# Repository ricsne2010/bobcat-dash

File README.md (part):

# M.O.S.S.: Maintenance, Operations, and Service System

(The `bobcat-dash` project.) A full-screen gauge display for a 1978 Bobcat M700 skid steer (Wisconsin VH4D 4-cylinder gas engine,
PerTronix electronic ignition), running on a Raspberry Pi.

| Gauge / light | Sensor | Green | Amber | Red |
|---|---|---|---|---|
| Battery, engine off | ADS1115 ch 0 through a voltage divider | 12.2–14.8 V (`CHARGING` at 13.2 V and up, e.g. a battery charger) | 11.8–12.2 V (LOW), 14.8–15.5 V (HIGH) | < 11.8 V or > 15.5 V |
| Battery, engine running | same | 13.2–14.8 V (CHARGING) | 12.0–13.2 V (NOT CHARGING), 14.8–15.5 V (HIGH) | < 12.0 V or > 15.5 V |
| Fuel level | ADS1115 ch 1, fuel sender | > 25 % | ≤ 25 % | ≤ 12 % |
| Tachometer | GPIO 17, from the ignition coil's negative terminal (PerTronix) through the board's coil input | 800–3050 rpm (VH4D governed ≈2950 no-load) | LOW IDLE (600–800 rpm for 1 s while running), 3050–3200 rpm | ≥ 3200 rpm (overspeed) |
| Engine oil pressure | GPIO 22, original switch through an optocoupler | OK | | LOW (flashing) |
| Hydraulic filter bypass | ADS1115 A2, monitored (4.7 kΩ resistor at the switch) | OK | | BYPASS (flashing) |
| Hydraulic oil temp | ADS1115 A3, monitored (4.7 kΩ resistor at the switch) | OK | | HOT (flashing) |

The battery panel switches between its engine-off and engine-running limits automatically, and its
color bar redraws to match. A caption in the panel's corner shows which set is active.

Grey means **no signal**: a broken wire, an unplugged sender, or an ADC that isn't answering. The filter
and temp switches are **monitored**: a resistor at each switch lets the dash spot a broken or unplugged
wire, which otherwise would look like a healthy open switch (see [End-of-line resistors](#end-of-line-resistors-filter-and-temp-switches)). The
header shows a summary: `ALL OK`, `CHECK n`, or a flashing `n ALARMS`. Every threshold is
in `config.toml`.

On startup, all warning tiles flash red for 2 seconds as a **lamp test**, like an old bulb check.
With the engine stopped, the oil-pressure switch is always closed, so that tile shows grey
`ENGINE OFF` instead of red.

The **tach decides** whether the engine is running. If it reads 0 rpm but the battery is at charging
voltage (13.2 V or more), the **oil pressure switch** settles it:

| Tach | Battery | Oil pressure | Means | Dash shows |
|---|---|---|---|---|
| 0 rpm | 13.2 V+ | none | Parked with a **battery charger** connected | `ENGINE OFF`, green `CHARGING`, no warnings |
| 0 rpm | 13.2 V+ | present | Engine running, **tach sensor dead** | `ENGINE RUNNING`, amber `CHECK SENSOR` on the tach |

Once a dead tach has been seen on a running engine, the dash remembers it until the alternator voltage
drops (engine stopped) or the tach reads again. If oil pressure is lost in that time, it's still a red
alarm with the horn. A charger on a parked machine can't set off the horn, and a dead tach can't hide
low oil pressure.

---

## Parts list

The full list with part numbers and quantities is the spreadsheet [`docs/bobcat-dash-BOM.xlsx`](docs/bobcat-dash-BOM.xlsx) (made by `tools/diagrams/make_bom.py`). The main parts:

| Part | Notes |
|---|---|
| Raspberry Pi 4 (2 GB is plenty) or Pi 5 | |
| Weatherproof HDMI monitor with its own 12 V supply, 1024×768 or similar | Any resolution works because the layout scales. Sunlight-readable (≥ 800 nits) helps a lot outdoors. Wiring: see [Monitor and boot splash](#monitor-and-boot-splash). |
| 12 V automotive relay (30/40 A, with socket) + fuse holder | Feeds the LED lights through the key. See [Lights](#lights). |
| 3× inline fuse holder, 1 A | One on each light sense wire, where it taps into the light circuit |
| ADS1115 16-bit ADC breakout | I2C, 4 channels: battery, fuel, filter, temp |
| 2× PC817 optocoupler | Oil pressure and tach. Keeps 12 V off the Pi. |
| 12 V → 5 V automotive buck converter, **5 A** (8–36 V input) | Don't use a cigarette-lighter USB plug. Pi 5 needs 5 A. |
| Inline fuse holder, 3 A | On the 12 V feed from the ignition switch (hand-wired). With the breakout board rev 2.0: 7.5 A at the battery on the constant feed, plus 2 A on the IGN wire. |
| Resistors: 47 kΩ, 4× 10 kΩ, 220 Ω, 2× 2.2 kΩ, 3× 4.7 kΩ, 100 Ω | |
| 2× 4.7 kΩ ½ W metal film resistor | **End-of-line resistors**, fitted at the filter and temp switches |
| 8× BAT85 Schottky diode | Clamp the ADC inputs (one to 3.3 V, one to GND, per input A0–A3) |
| 2× 1N4148 diode, 4× 0.1 µF capacitor | |
| Tach signal: a wire from the ignition coil's **negative** terminal | This machine (PerTronix + Flame-Thrower 40611 coil) uses the breakout board's COIL input (its own `COIL` plug since rev 2.4). A NJK-5002C Hall sensor + magnet on the crank pulley is the alternative, and the only option when hand-wiring. |
| Weatherproof enclosure, Deutsch/Weatherpack connectors | Vibration kills loose Dupont jumpers |

## Wiring

All Pi-side grounds connect together: Pi GND, ADS1115 GND, and the optocoupler output side.
The 12 V side of the optocouplers stays separate from the Pi side.

```
POWER (hand-wired: the Pi loses power the moment the key is turned off)
  Ignition switch (+12V) ──[3A fuse]──> Buck converter IN+ ──> 5V OUT ──> Pi USB-C / 5V pins
  Chassis ground ──────────────────────> Buck converter IN- ──> GND

POWER (breakout board rev 2.0: clean shutdown at key-off, see "Key-off shutdown")
  Battery + ──[7.5A fuse, at the battery]──> board POWER IN "BAT+"   (constant, always live)
  Key switch IGN terminal ──[2A fuse]──────> board POWER IN "IGN"    (a few mA: sense only)
  Chassis ground ──────────────────────────> board POWER IN "GND"
  Board "TO BUCK" ──> Buck converter IN+ / IN-  (switched by the board)

ADS1115                     Pi
  VDD ───────────────────── 3.3V (pin 1)
  GND ───────────────────── GND  (pin 6)
  SDA ───────────────────── GPIO2 / SDA (pin 3)
  SCL ───────────────────── GPIO3 / SCL (pin 5)
  ADDR ──────────────────── GND  (address 0x48)

BATTERY VOLTAGE  -> ADS1115 A0
  +12V (ignition) ──[47k]──┬──────────> A0
                           ├──[10k]───> GND
                           ├──[BAT85, band toward 3.3V]──> 3.3V
                           ├──[BAT85, band toward A0]────> GND
                           └──[0.1µF]──> GND
  The BAT85s only conduct if A0 goes above 3.3 V or below 0 V. Don't use a 3.3 V zener here:
  low-voltage zeners leak tens of µA, which would pull the battery reading low.
  Ratio = (47+10)/10 = 5.7, so 15.5 V reads as 2.72 V on the ADC.

FUEL SENDER  -> ADS1115 A1
  Setup A, sender wired only to the dash:
      3.3V ──[220Ω]──┬──> A1           (+ two BAT85 clamps and 0.1µF, as for A0)
                     └──> sender terminal (the sender grounds through the tank)
  Setup B, an analog gauge as well (a backup if the Pi or monitor fails):
      12V (key) ──> gauge ──> sender terminal ──[47k]──┬──> A1   (no 220Ω pull-up)
                                                        └──[10k]──> GND
  The breakout board does either with jumpers JP1/JP2. Calibrate with --calibrate (below).

OIL PRESSURE SWITCH  -> GPIO 22, through an optocoupler
  The oil switch closes to ground when pressure is low.

  +12V (ignition) ──[2.2k]──> PC817 LED anode (+)
  PC817 LED cathode (-) ────> oil switch terminal
  1N4148 across the LED, reversed (protects it from voltage spikes)

  PC817 collector ──> GPIO 22      (Pi internal pull-up is enabled)
  PC817 emitter ────> Pi GND

  Switch closes -> LED lights -> GPIO pulled low -> alarm.

HYD FILTER BYPASS + HYD OIL TEMP SWITCHES  -> ADS1115 A2 / A3, monitored
  At each switch: a 4.7k "end-of-line" resistor from the switch terminal to ground
  (see "End-of-line resistors" below). At the Pi end, for each switch:

  3.3V ──[4.7k]──┬──[10k]──┬──> A2 (filter) / A3 (temp)
                 │         ├──[BAT85, band toward 3.3V]──> 3.3V
                 │         ├──[BAT85, band toward A2]────> GND
                 │         └──[0.1µF]──> GND
                 └──────────> switch wire (to the switch + its 4.7k resistor)

  Wire reads ~1.65 V = OK, ~0 V = switch closed (alarm), 3.3 V = wire broken (NO SIGNAL).
  Nothing else may connect to these two switches (no lamps): any 12 V on the wire reads as "broken".

  Optional status LEDs driven by the Pi: GPIO 23 (filter) / GPIO 24 (temp) ──[470Ω]──> LED ──> GND.
  On = switch closed, blinking = wire broken, off = OK.

TACH  -> GPIO 17   (hand-wired: Hall sensor only. For the ignition coil, use the breakout board's COIL input.)
  NJK-5002C Hall sensor: brown = +12V, blue = ground, black = signal (NPN, pulls low near a magnet)
  +12V ──[2.2k]──> PC817 LED anode;  LED cathode ──> sensor black wire
  PC817 collector ──> GPIO 17, plus a 4.7k pull-up to 3.3V (faster edges than the internal one)
  PC817 emitter ──> Pi GND
```

> **Tach from the ignition coil (this machine).** The Wisconsin VH4D has a PerTronix electronic
> distributor and a Flame-Thrower 40611 coil (3.0 Ω). The tach reads the coil's **negative (−)
> terminal**, the same place a normal aftermarket tach connects, on the breakout board's **COIL** plug (the
> 2-pin plug on the board's left edge, inside the boxed HIGH VOLTAGE corner; rev 2.4). Each spark is one pulse, and a 4-cylinder four-stroke fires twice per crank turn, so
> `pulses_per_rev = 2.0`.
>
> That terminal jumps to about 300–400 V every time the coil fires, so it must **only** go to the COIL
> plug, never to TACH SIG or any other input. The board's coil input is built for it: two ½ W resistors take the
> voltage, a 15 V zener clamps it, and a 1 µF capacitor smooths the coil's ringing so each spark gives one
> clean pulse into its own optocoupler. The software also ignores anything within 3 ms of a pulse
> (`min_pulse_gap_ms`), as a second line of defence. Run a 20 AWG wire from the coil − terminal to the
> board, away from the spark plug leads. Shielded wire is better still: connect the shield's drain to the
> COIL plug's GND pin and leave it unconnected at the coil end. Per PerTronix, this coil needs **no ballast resistor** or resistance
> wire in its + feed.
>
> No sensor, magnet or bracket is needed on the crank pulley. The trade-off: if the ignition stops, the tach
> reads 0. That's fine, because the engine has stopped too.

## Low idle and cool-down

**LOW IDLE** (amber, one soft beep). If the engine is running but sits below 800 rpm for more than
a second, the RPM pill turns amber and reads `LOW IDLE`. The dial shows the same band in amber, from
600 to 800 rpm. A sagging idle usually means a stall is coming: fuel starving, a plugged
fuel filter, the choke left on, or carb icing. It's ignored for the first 5 s after start-up.
Set `low_idle_below = 0` in `[tach]` to turn it off.

**Cool-down reminder** (information only: no sound, and not a warning). The VH4D is air-cooled, and the
repair manual says to idle it at 1000–1200 rpm for 3–5 minutes after hard running before shutting off.
The dash keeps track:

1. Time at or above 2000 rpm adds up as hard work. Short dips don't reset it.
2. Once there's 5 minutes of it, bring the hand throttle back to idle (1300 rpm or below). The RPM pill
   then counts down: `COOL DOWN 2:40`.
3. Rev above 1300 rpm and the countdown starts over. At part throttle (1300–2000 rpm) the pill says
   `IDLE TO COOL DOWN`.
4. When it's done: `OK TO SHUT DOWN` in green for a minute.

Stopping the engine clears it. The numbers are in `[cooldown]` in `config.toml`.

## Machine angle (roll and pitch)

The **MACHINE ANGLE** panel shows the machine from behind (roll, side to side) and from the side (pitch, nose
up or down). The outlines tilt with the machine, over a dashed level line, with the angle in degrees and which
way it's leaning. Battery and fuel share the panel above it, and the warning tiles are a little shorter to make
room.

| | Amber `STEEP` (one beep) | Red `TIP RISK` (alarm tone + horn) |
|---|---|---|
| Roll (either side) | 8° | 15° |
| Pitch, nose up | 15° | 20° |
| Pitch, nose down (backing up a steep incline) | 20° | 25° |

**These limits are not from Bobcat.** Bobcat's manuals give no angles: they say to keep the heavy end of the
loader uphill and to travel straight up and down slopes, never across. These defaults are chosen for this
machine: roll warns earliest because side slopes are where a skid steer is least stable, and nose down allows
the most because steep inclines are backed up, with the nose pointing downhill and the heavy end uphill. Change them in `[tilt]`, and use
lower limits if you often work with a loaded or raised bucket. An angle must last 0.5 s before it shows (a bump
isn't a slope), and clears 1° back inside the limit.

**Sensor:** an **LSM6DSOX** accelerometer + gyro board (Adafruit 4438, or the LSM6DS3TR-C, Adafruit 4503). It plugs
into the breakout board's latching **TILT** connector (Molex Micro-Fit 3.0, rev 2.6): pin 1 GND, 2 3V3, 3 SDA,
4 SCL. Make the cable from 22–24 AWG wire (4-core shielded is best): a Micro-Fit housing 43645-0400 with four
43030-0007 crimp pins at the board end, and the other end soldered straight into the sensor board's VIN, GND,
SDA and SCL holes (its small STEMMA QT socket is friction-only and would shake loose). It shares the Pi's I2C
bus with the ADS1115.

**Cable length:** I2C is meant for short runs, and a skid steer is electrically noisy. Under ~30 cm is ideal;
up to ~50 cm is fine routed away from the coil and plug leads (shielded 4-core is better, shield grounded at
the board end only). Up to ~1 m, also slow the bus with `dtparam=i2c_arm_baudrate=50000` in
`/boot/firmware/config.txt`. Further than that, use a differential I2C extender (e.g. SparkFun QwiicBus,
PCA9615). The dash blends the gyro and accelerometer, so
braking, bouncing and turning don't make the angle jump.

- **Mount it rigidly** to the frame, or inside a dash box that's bolted solidly to it (not on rubber
  isolators). Flat, with the board's **X arrow pointing forward**. Other orientations: `axes` and `upside_down`
  in `[tilt]`.
- **Zero it once**, parked on level, firm ground with the engine off: `python3 dash.py --zero-tilt`. It saves
  the level point (and the gyro's small offset) in the data folder, where it stays through every key-off. It
  refuses if the sensor reads more than 5° off level (parked on a slope, or the sensor mounted crooked) or if
  the readings move (engine running, someone climbing on). Add `--force` only if you're sure the machine is
  level.
- **Parking and restarting on a slope is fine.** Nothing needs remembering: gravity gives the true angle at
  every start-up. The first second is averaged (during the boot splash) so engine vibration doesn't skew
  it. If you're parked past a limit, the panel says so as soon as the dash is up.
- **If the sensor is missing or fails, the panel shows grey NO SIGNAL, never a guessed "level".** It counts
  as `CHECK` in the header and plays the connection-lost sound once; nothing else on the dash is affected.
  The dash keeps trying: a sensor plugged in later is picked up within about 2 s. A plug that works loose
  and back in, or a power blip, makes the chip restart powered down and read all zeros; that's caught
  (along with any reading where gravity isn't about 1 g, or the chip losing its settings), and the sensor is
  set up again and re-averaged for a second before an angle shows. A single glitchy read is ignored. Each
  problem is written once to the log (`journalctl -u bobcat-dash`).
- To leave tilt out entirely, set
  `enabled = false` in `[tilt]`: the screen goes back to the original layout (separate battery and fuel panels,
  taller warning tiles).

## Temperatures

The header shows temperatures next to **BOBCAT**: the electronics box (E-box) air, then your probes.

```
BOBCAT   E-BOX 100°F   CAB 92°F   OUT 104°F          ENGINE RUNNING              ALL OK
```

- **E-BOX** (electronics box) is the DS18B20 on the breakout board (rev 2.7): the air inside its enclosure. Above **50 °C
  (122 °F)** it turns into an amber **E-BOX HOT** pill (one beep, counts in `CHECK`); above **65 °C (149 °F)** red
  (alarm tone, no horn). The breakout board's own parts are rated well above that; the limits warn you that
  the box is cooking (no ventilation, direct sun) before anything else in it suffers. If the board sensor
  stops answering it shows grey `BOX --` (and the connection-lost sound).
- **Probes:** waterproof DS18B20 probes (stainless tip on a cable, 3-wire) plugged into the board's
  **TEMP PROBE** connector: red to 3V3, black to GND, yellow (or white) to DQ. Several can share the one
  connector (splice them together, or use a small junction). Each shows by the name you give it, e.g. `CAB`
  and `OUT`, or set `ambient = "average"` for a single `AMB` reading. A missing probe shows `--`.
- **Setup:** once, `dtoverlay=w1-gpio` in `/boot/firmware/config.txt` (see *Installing on the Pi*). Then
  `python3 dash.py --temps` lists every sensor with its ID and reading. Hold one in your fingers for 20 s and
  run it again to see which is which, then put the IDs in `[temperature]`: `board_id` and the `probes` list
  with names. With only the board sensor fitted, nothing needs setting.
- `units = "F"` (or `"C"`) sets what's shown; the E-BOX limits in `config.toml` are in °C.
- Simulator: **=** steps the box through normal, warm, hot and sensor missing; CAB and OUT are simulated.

## Cylinder head temperatures (CHT)

A Type K thermocouple under each spark plug, read by an MCP9601 thermocouple amplifier on the **CHT board**
(rev 3.0), which plugs into the breakout board's **CHT (I2C)** connector. Fit one to four: list the ones fitted in
the web page's **Configuration** page (or `[cht] cylinders`: the module in CHT-board socket 1-4 answers at 0x60, 0x65, 0x66, 0x67). Until then CHT is off.

- **Sensor:** The Sensor Connection **CHT-FS-072-06-18-K-MP** (flexible stem, rated to 1000 °C, *ungrounded*
  junction, 18 mm ring for the VH4D's plugs, male mini K plug). 120 in lead and custom lengths are available.
- **Extension:** only **Type K extension wire** and Type K (yellow) mini connectors between the sensor and the
  board: ordinary copper adds an error that changes with the temperature at the joint. US colours: yellow = +,
  **red = -**. Keep the plastic connectors away from the hot head.
- **On the dash:** a **CYL HEAD TEMP** tile beside the warning lights: the hottest cylinder big, every
  cylinder small underneath. On the web Status page: a tile with each cylinder; Reports: each cylinder's
  daily high and low while running (Extremes).
- **Limits** (°F, `[cht]`): **500 °F** amber CHT HIGH, **550 °F** red with the horn. The factory head
  switches on early Bobcat 700 engines stop the engine over **570 °F** (service manual 7A-3); M.O.S.S. warns
  before that and **never stops the engine itself**. **CHT SPREAD** (amber): with the engine running 5 min
  and warm, one cylinder 100 °F cooler than the average of the others (a fouled plug, misfire or plug wire).
  A broken or unplugged thermocouple shows that cylinder as `--` (NO SIGNAL).
- Simulator: **`** steps through normal / cyl 3 warm / cyl 3 hot / cyl 2 misfiring / cyl 4 unplugged.

## Parking brake

A sealed switch on the parking brake handle, closed when the brake is set, to the breakout board's
**PARK BRAKE** plug (on the CHT + Parking Brake board, GPIO 9). Turn it on once it's fitted: the web page's **Configuration** page (or `[park_brake] enabled = true`).

- **(P) BRAKE** (red) in the header while the brake is set.
- **PARKING BRAKE ON** (amber, flashing (P)): the brake is set while the engine works above idle for 5 s.
- **SET PARKING BRAKE** on the key-off countdown (with a beep) if it isn't set. A broken wire reads as
  "released", so this reminder also proves the switch works: set the brake and it goes away.
- Simulator: **/** sets / releases it.

## Pi health warnings

The dash also watches the Pi itself, and shows two amber warnings in the header (one beep each, and they
count in the header's `CHECK` total):

- **`PI HOT 84°C`**: the Pi's CPU is at or above 80 °C, or the Pi is already slowing itself down for heat.
  It protects itself (it slows down rather than failing), but that should never happen in normal use. It
  means the enclosure is cooking: add or fix the Pi's fan and heatsink, shade the box, or move it away from
  the engine side.
- **`LOW 5V`**: the Pi saw its 5 V supply sag. A weak or undersized buck converter, a thin or long 5 V wire, or
  the battery dipping below the buck converter's minimum input while cranking. It stays up for 10 s after each
  dip so a short sag isn't missed. Occasional dips while cranking are a sign to pick a buck converter rated
  down to 6–8 V input.

Settings are in `[pi_health]` in `config.toml`. On a computer that isn't a Pi they stay quiet. Simulator: **I**
(hot Pi) and **U** (low 5 V) turn each warning on and off.

## Charging system (Delco 10SI)

This machine uses a Delco 10SI 3-wire alternator (internal regulator) in place of the old generator and
external regulator. The wiring is in [`docs/wiring-schematic.jpg`](docs/wiring-schematic.jpg), section 7:

- **BAT stud:** 8 AWG to the battery + through a fusible link or breaker (10 AWG for a 45 A unit).
- **Terminal 2 (sense):** 18 AWG to the battery +, the same point as the board's `BAT+`. The regulator then
  holds the voltage the dash measures.
- **Terminal 1 (excite):** from the key's ON/RUN circuit through a **1N4001 diode** (band toward the
  alternator) and a **47 Ω 5 W resistor**. There's no charge lamp: the dash shows **NOT CHARGING** instead.
  - The diode stops the running alternator feeding ~14 V back into the ON circuit. Without it the PerTronix
    stays powered after key-off (the engine keeps running), and the dash never sees the key go off.
  - The resistor limits the current with the key on and the engine stopped to about 0.25 A, what a charge
    lamp passes. Terminal 1 feeds the alternator's field, so with the diode alone that current is 3-4 A:
    more than a 1N4001's rating, and a flat battery if the key is left on.
- **Grounds:** a heavy, clean engine-to-frame strap. The alternator grounds through its case.

**Starting.** While the starter cranks, a healthy battery sags to about 10 V. The dash recognises cranking
(the coil fires, so the tach reads about 150–300 rpm before the engine catches) and shows an amber **CRANKING**
on the battery and RPM panels and in the header: no alarm, no horn. Below 9.6 V while cranking it says
**WEAK CRANK** instead, a sign of a tired battery or a poor starter cable or ground. For the first 10 s after
the engine catches, a low reading shows **STARTING UP** rather than NOT CHARGING, while the battery recovers and
the 10SI comes up to voltage.

If it **doesn't start** and you let go of the key, the panel goes back to `ENGINE OFF`. The battery shows
`RECOVERING` for a second or two while it climbs back from the starter dip, then its normal reading (about
12.4–12.5 V after a failed attempt): no alarm.

**Starter rest.** Crank for more than 10 s without a start and the header and RPM panel say **REST STARTER**,
with a beep at once and every 5 s while you keep cranking. Let go of the key and the header counts down
**STARTER COOLING 0:29** (the RPM panel shows `REST 0:29`); at zero it shows **READY TO START** in green for a
few seconds. Crank again before the countdown ends and REST STARTER comes straight back, and the countdown
starts over when you let go. It's a reminder only: the starter is wired to the key, not the dash. Use the rest
to check fuel and spark.

The limits are `crank_low`, `crank_detect`, `crank_recover` and `start_grace` in `[voltage]`, and
`crank_limit` (10 s) and `crank_rest` (30 s) in `[tach]`.

**Check after installing:** at a fast idle, a meter at the battery reads about 13.9-14.6 V (the 10SI lowers it
as it warms up). Set `divider_ratio` in `[voltage]` so the dash agrees. Then turn the key off: the engine must
stop, and the dash must count down `KEY OFF`.

## Engine hour meter

A Hobbs-style hour meter sits at the bottom of the RPM panel: `HOURS 1234.5`, four digits and
tenths, with the tenths wheel inverted like a mechanical meter. The tenths wheel **turns
continuously**: it takes 6 minutes (0.1 hour) to roll to the next digit, so after a short run it may
still read the same number. A small green dot pulses while it's counting.

- **It counts only while the engine is running**, using the same running logic as the oil warnings
  (tach, or alternator + oil pressure if the tach sensor has failed).
- **It never resets.** There's no reset on the screen or in `config.toml`. After 9999.9 it rolls
  over to 0000.0, like a mechanical meter, but the full total is kept in the file.
- **Saving:** the meter saves whenever the engine stops, and every 15 seconds while it runs. With the
  breakout board rev 2.0, turning the key off stops the engine, the meter saves, and the Pi shuts down
  cleanly, so **nothing is lost at key-off** (see [Key-off shutdown](#key-off-shutdown)). The 15-second save
  only matters if power is cut unexpectedly (a blown fuse, a battery disconnected with the engine running,
  or a hand-wired setup without the power-hold circuit): then at most about 15 seconds is lost. It keeps
  two copies with checksums, so a power cut in the middle of a save can't lose the total.
- **Where it's kept:** `~/bobcat-dash-data/hours_a.json` and `hours_b.json` (set by `data_dir` in
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
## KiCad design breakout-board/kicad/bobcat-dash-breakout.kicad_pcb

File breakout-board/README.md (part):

# Bobcat Dash Breakout Board (rev 3.0)

A 162 × 159 mm, 2-layer, all through-hole PCB that sits between the machine's wiring harness and
the Raspberry Pi. Every harness wire lands on a labeled, unpluggable terminal. Every signal has a
status LED or a test point, so you can find a fault with a multimeter and your eyes. Rev 2.0 adds a
**power-hold circuit**: after key-off, the Pi saves the engine hours and shuts down cleanly before the
board turns the power off. Rev 2.1 adds **light sensing**: the dash shows when the front, rear or work
lights are switched on. Rev 2.2 adds a **coil tach input**: the RPM comes straight from the ignition coil, so no
crank sensor is needed. Rev 2.4 gives the coil wire its own plug in a fenced-off **high-voltage corner**, and
outlines every circuit block on the silkscreen. Rev 2.5 adds a **TILT** connector for the roll / pitch sensor; rev 2.6 makes it a latching Molex Micro-Fit. Rev 2.7 adds **temperature**: a sensor for the box's air and a latching connector for external probes. Rev 2.8 takes the current Adafruit ADS1115 board (two header rows) plugged straight in.

## What's on it

| Section | What it does |
|---|---|
| **Harness connectors** (bottom edge) | 8 pluggable 5.08 mm screw-terminal headers, plus the `COIL` plug on the left edge. Each plug pulls off as a block for testing. Every pin is labeled. |
| **Circuit outlines** (rev 2.4) | Every block has a silkscreen outline with its name: POWER LEDS, TEST POINTS, POWER IN / FUSES / HORN DRIVER, ENGINE + HYDRAULIC INPUTS, BATTERY / FUEL / BUTTON, LIGHTS ON, POWER HOLD. |
| **Fuses** | F1 main feed (5 A, for a Pi 4 or a Pi 5), F2 horn (1 A). Mini blade fuses in board-mounted holders. |
| **Protection** | D1 (P6KE20A TVS) clamps voltage spikes. If power is connected backwards, it conducts and blows F1 instead of damaging anything. |
| **Power hold** (bottom band) | Q2 (P-MOSFET) switches the constant battery feed on while the key is on **or** the Pi holds it on. A yellow `KEY` LED shows the key position, a green `HOLD` LED shows the Pi is holding the power. U6 (CD4060 timer) cuts the power 3 minutes after key-off if the Pi hasn't. See [Power hold](#power-hold-rev-20). |
| **Power LEDs** (green) | `12V ON`, `HORN/F2`, `5V`, `3V3`: an unlit LED means the power is off, a blown fuse or a missing supply. |
| **Oil + tach inputs** | Each through a PC817 optocoupler. A **yellow LED lights whenever the input is active** (switch closed / tach pulse). |
| **Coil tach input** (rev 2.2, own corner in rev 2.4) | The `COIL` plug J12 on the **left edge** takes the ignition coil's **negative** terminal, which spikes to ~400 V when it fires. It sits in a **HIGH VOLTAGE** corner with a double outline and warning triangles, like the HV section of an old CRT monitor: everything that sees the raw coil voltage (J12, R80, R81) is inside it, joined by under 15 mm of trace. Two ½ W resistors, a 15 V zener and a 1 µF filter turn the spikes into one clean pulse per spark; only that clamped (≤ 15 V) signal leaves the corner, to optocoupler U10. The yellow `COIL` LED flickers with the engine. It shares the Pi's tach pin with the Hall input (TACH `SIG`): connect **one or the other**. The `COIL` plug's second pin is GND, for a shielded wire's drain. |
| **Filter + temp inputs** | **Monitored** on ADC inputs A2 / A3. With a 4.7 kΩ resistor fitted **at each switch** (see below), the dash can tell OK, switch closed and **broken wire** apart. Their yellow LEDs are driven by the Pi: **on = switch closed, blinking = wire broken**, off = OK. |
| **Light sensing** (right side) | Three PC817 inputs, one per light: front, rear, work. Each takes a sense wire from the **lamp side** of a light switch (a few mA; the lamps' own current never comes through the board). A **yellow `FRONT` / `REAR` / `WORK` LED** lights while that light is on, and the dash shows a matching symbol. |
| **Horn driver** | IRLZ44N MOSFET with a pull-down, so the horn stays off while the Pi boots. **Red `HORN ON` LED** shows when the Pi is switching it on. |
| **Analog** | Battery divider (A0), fuel sender (A1), filter (A2) and temp (A3), all with Schottky clamps and filtering. All four ADC inputs are in use. |
| **Modules** | Sockets for the ADS1115 ADC board and the MAX98357A amplifier board. The outlines show where each module sits. **Amp: fit one of two.** The **mono** board (Adafruit **3006**) goes on **J9** (`LRC BCLK DIN GAIN SD GND VIN`), screwed down through **H9–H10** at its far edge. The **stereo** board (Adafruit **6513**, two MAX98357As) goes on **J16** in the top strip (`VDD GND BCLK LRC DIN GAIN`, no SD), screwed down through **H11–H14** at its corners. Same signals, same software; on the stereo board use the LEFT speaker output (or both). Never fit both: they'd share the same I2S lines. The ADS1115 (Adafruit **1085**, STEMMA QT version) plugs straight in on two 6-pin sockets 12.7 mm (0.5") apart: **J10** for its bottom row `VIN GND SCL SDA ADDR ALRT`, **J15** for its top row `A+ A3 A2 A1 A0 A-`. ADDR is grounded (address 0x48); A+ and A- are the module's own filtered analog supply (outputs) and are left open. Four M2.5 holes (**H5–H8**) line up with the module's corner holes so it can be screwed down on standoffs against vibration (see *Parts to buy*). |
| **Test points** | 16 labeled test points in a strip: power rails, three GND loops for your meter's black lead, and every signal. Four more next to the power hold: `FUSED 12V`, `IGN`, `HOLD`, `TIMER`. |
| **TILT connector** (rev 2.5, latching since 2.6, top right beside the ADC module since 2.9) | J13, a **Molex Micro-Fit 3.0** 4-pin header (43650-0415) with a positive latch, for the machine-angle sensor (LSM6DSOX, Adafruit 4438), on the Pi's I2C bus with the ADS1115. Pins **1 GND, 2 3V3, 3 SDA, 4 SCL**. Cable side: housing 43645-0400 with four 43030-0007 crimp pins (22–24 AWG, ideally 4-core shielded); solder the other end straight into the sensor board (its STEMMA QT socket is friction-only). 100 Ω in SDA and SCL (R83, R84) protect the Pi's pins and soften noise on the cable; 47 Ω in the 3.3 V feed (R85) limits a shorted cable to ~70 mA, so the Pi's 3.3 V (which also feeds the ADS1115) stays up. Keep the cable under ~30–50 cm. |
| **AUX (CHT + BRAKE)** (rev 3.0, J18, bottom right under the TEMP column) | A latching **Molex Micro-Fit 3.0 2×3** (43045-0612) to the **CHT + Parking Brake board** ([cht-board](cht-board/README.md)) in the electronics box: pins **1 GND, 2 3V3, 3 SDA, 4 SCL, 5 BRAKE, 6 BRAKE 12V**. The I2C lines share the TILT plug's protection (100 Ω in SDA / SCL, 47 Ω in 3V3: same bus, and this cable stays inside the box). The parking brake's optocoupler is on the CHT board: its LEDs are fed from +12V through **R97 2.2k** (a shorted cable draws ~5 mA) and the signal comes back to **GPIO 9** (Pi pin 21) through **R96 1k**. Cable: two housings 43025-0600, pin 1 to pin 1. |
| **BUTTON POD** (rev 2.9, J17, next to the ADC module) | One latching **Molex Micro-Fit 3.0 8-pin** (43650-0815) to the button pod on top of the box (`enclosure/button-pod`): pins **1 LEFT, 2 RIGHT, 3 OK, 4 BACK, 5 SILENCE, 6 GND, 7 FAN +12V, 8 FAN −**. Each button input gets 1 kΩ in series and 100 nF to GND (R89–R92, C12–C15), like SILENCE; pin 5 is wired to the SILENCE plug J8, so either works. Pi pins: LEFT GPIO 8, RIGHT GPIO 7, OK GPIO 20, BACK GPIO 10. **Pod fan:** a 12 V fan switched by **Q5** (IRLZ44N, the same as the horn) from GPIO 11, with R94 holding it off while the Pi boots, D46 flyback and a green **FAN ON** LED (D47). Cable side: housing 43645-0800, 8 × 43030-0007 pins. |
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
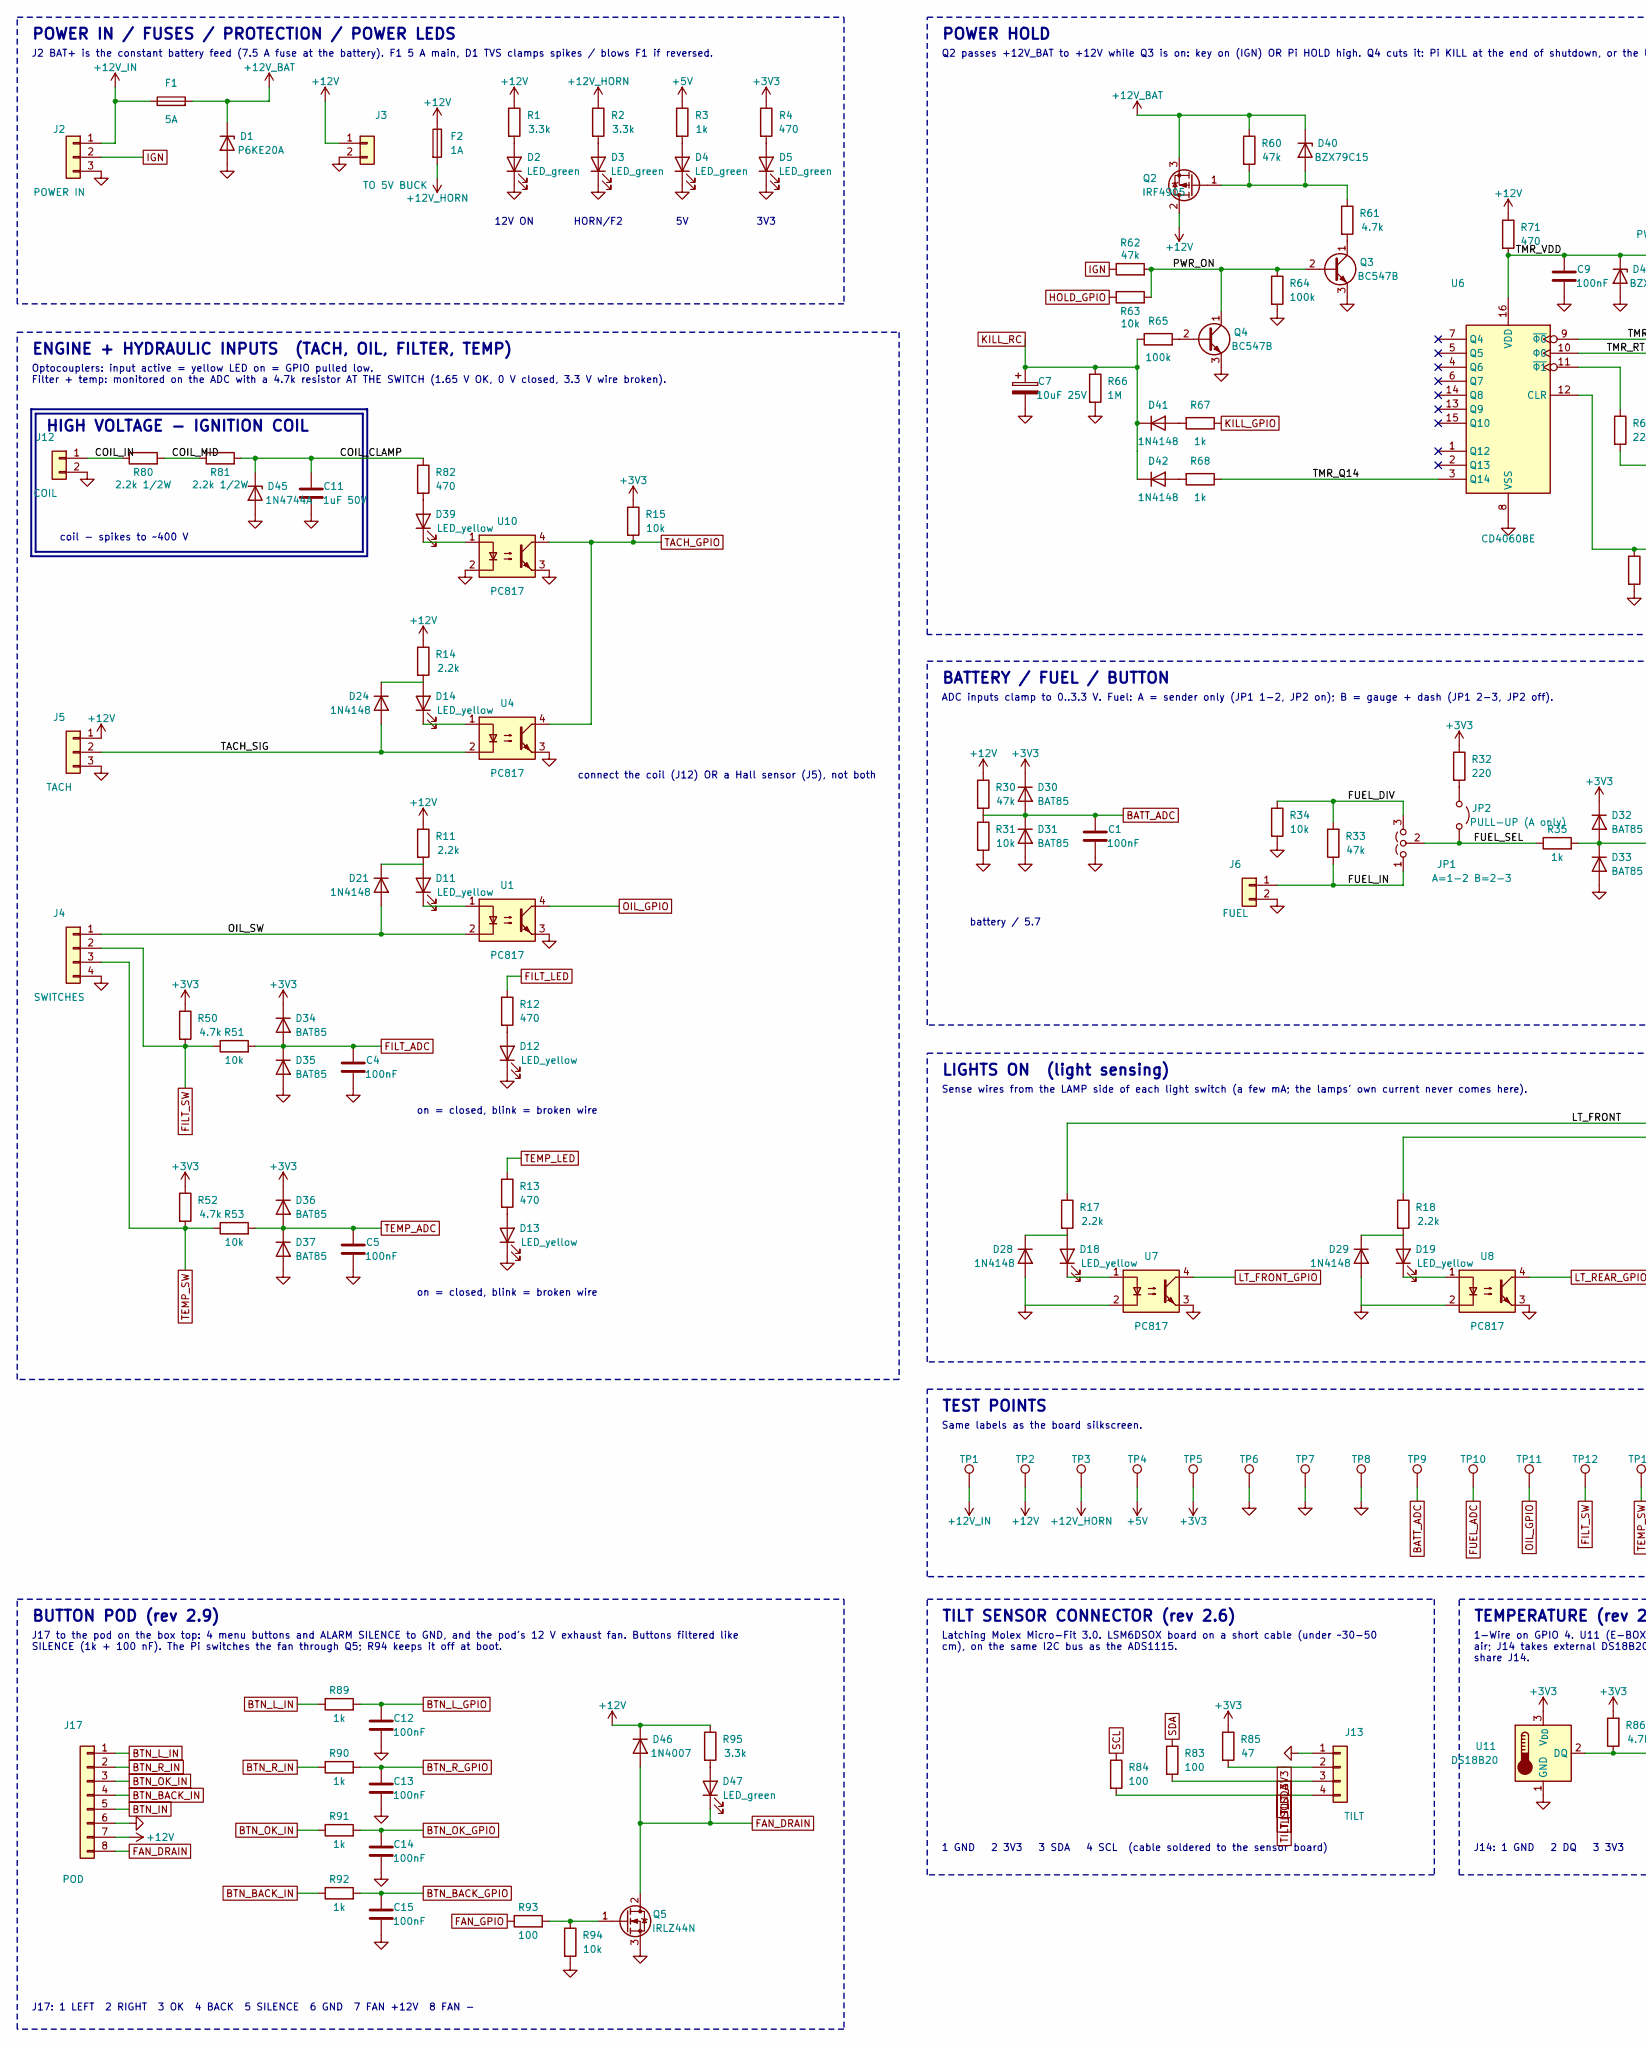
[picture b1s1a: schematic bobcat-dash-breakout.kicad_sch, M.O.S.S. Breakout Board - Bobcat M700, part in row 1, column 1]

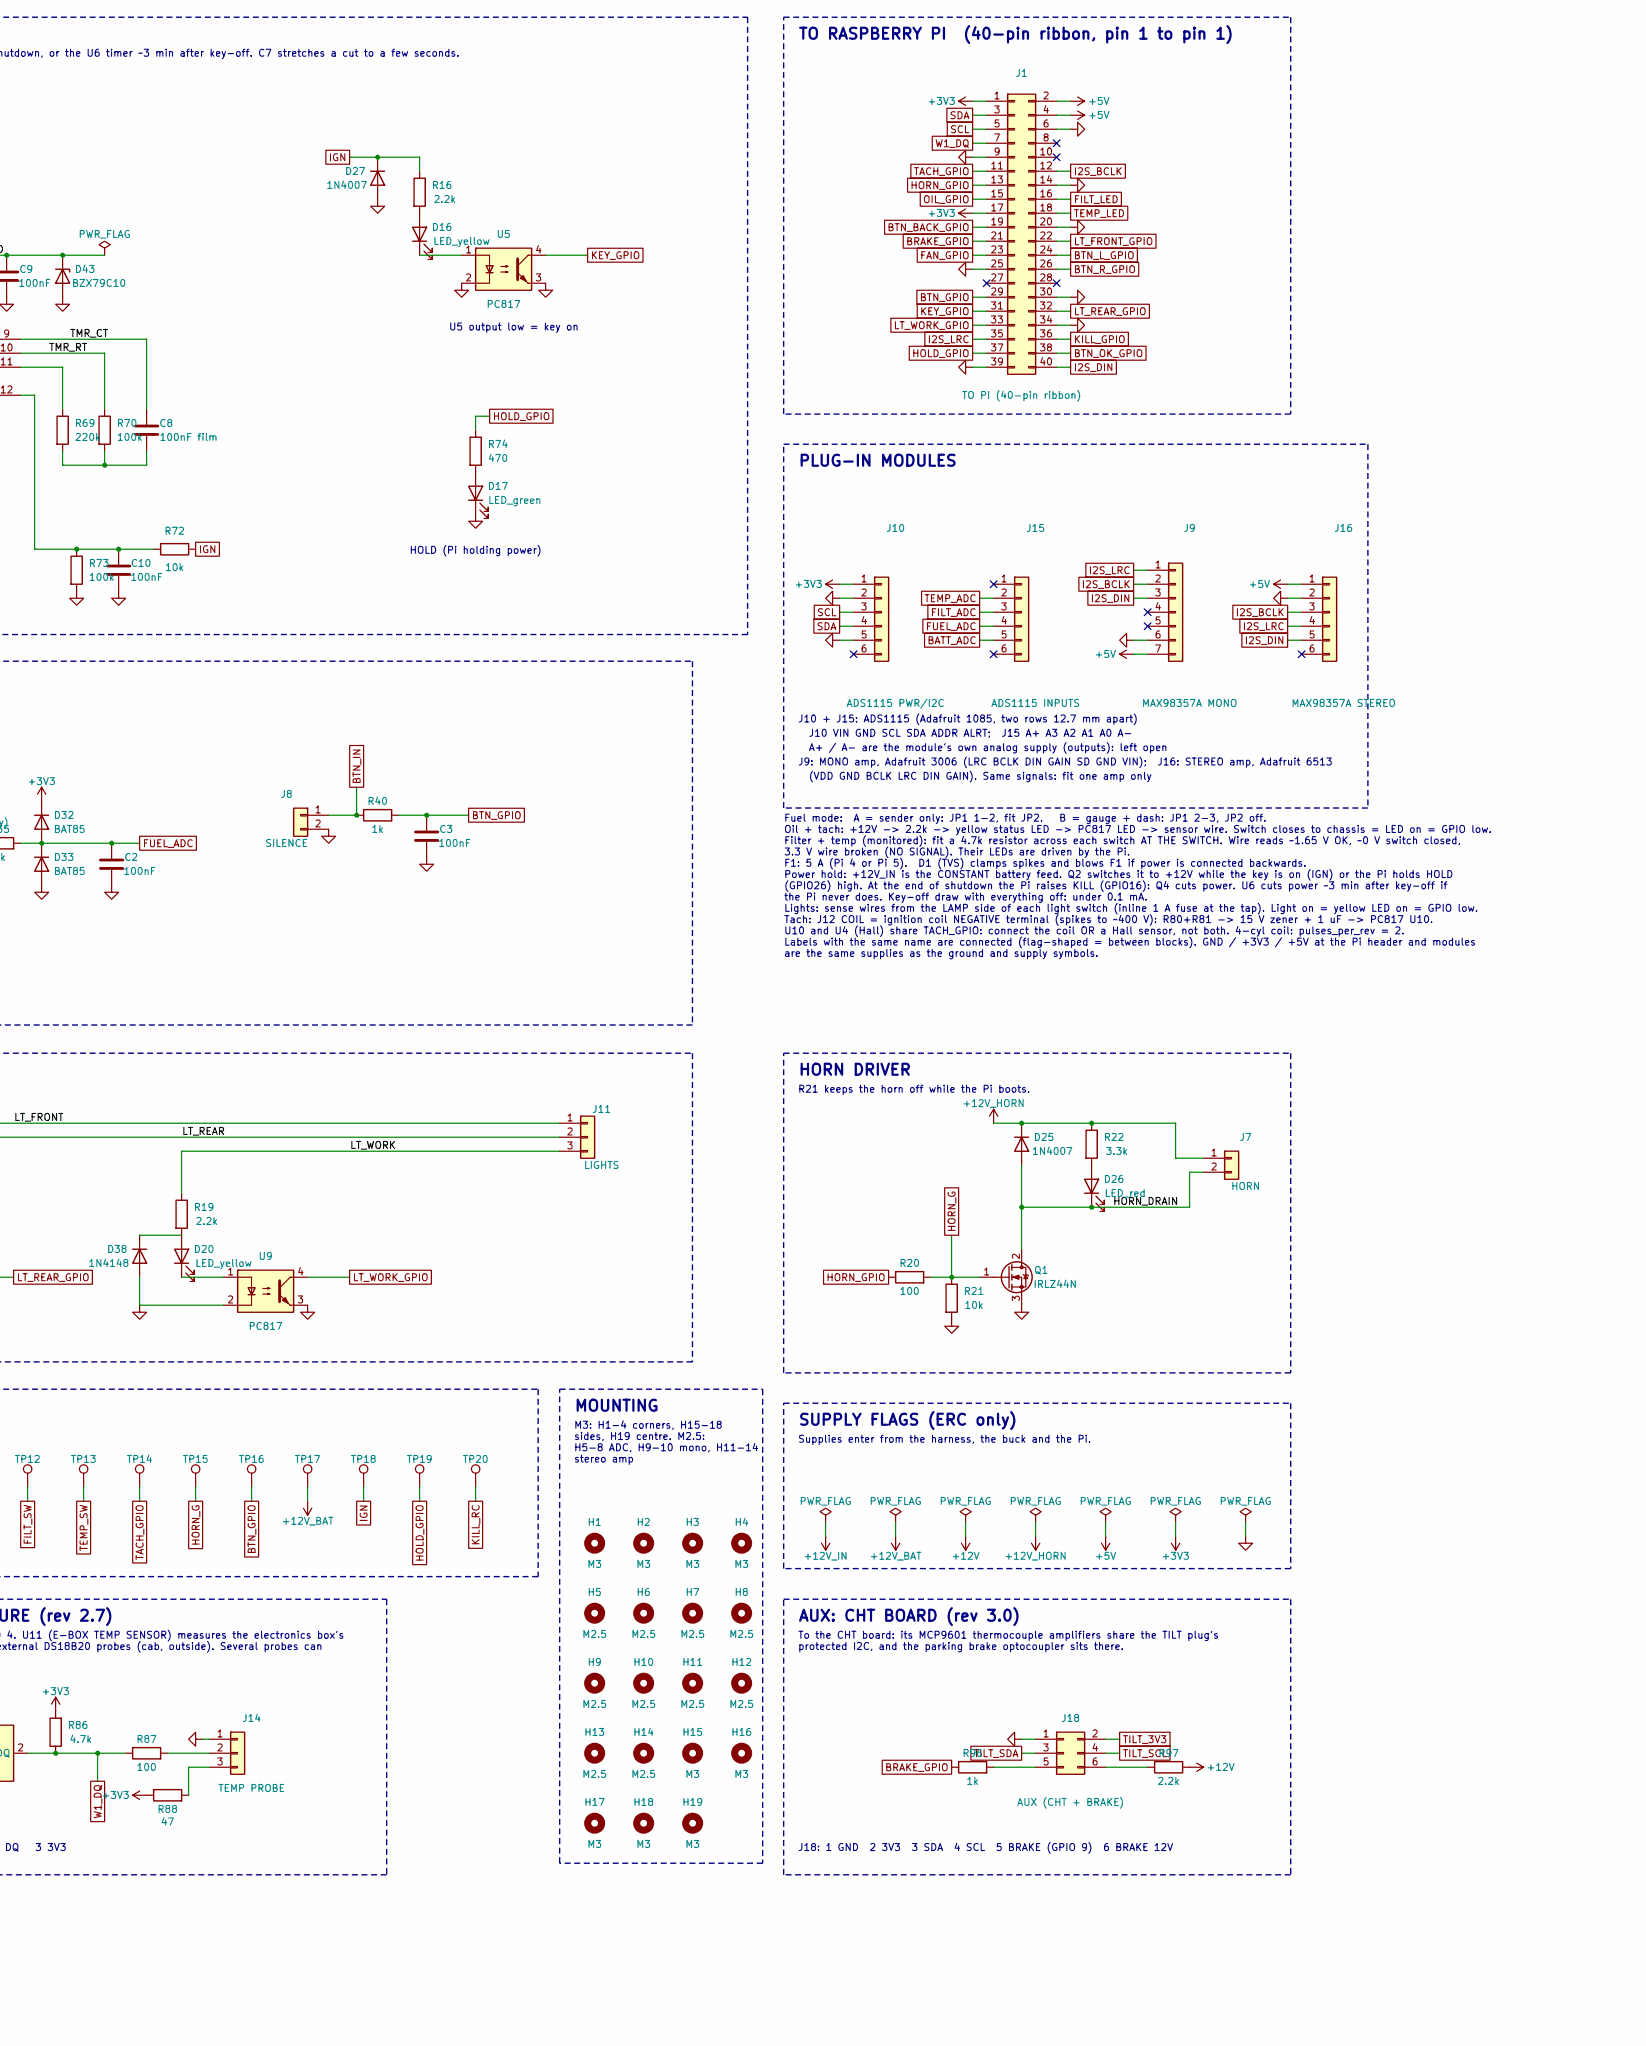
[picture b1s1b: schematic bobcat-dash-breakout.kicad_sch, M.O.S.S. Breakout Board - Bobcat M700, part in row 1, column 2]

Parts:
C1, C2, C3, C4, C5, C9, C10, C12, C13, C14, C15: 100nF; C_Disc_D5.0mm_W2.5mm_P5.00mm
C7: 10uF 25V; CP_Radial_D5.0mm_P2.00mm
C8: 100nF film; C_Disc_D5.0mm_W2.5mm_P5.00mm
C11: 1uF 50V; C_Disc_D5.0mm_W2.5mm_P5.00mm
D1: P6KE20A; D_DO-15_P12.70mm_Horizontal
D2, D3, D4, D5, D17, D47: LED_green; LED_D3.0mm
D11, D12, D13, D14, D16, D18, D19, D20, D39: LED_yellow; LED_D3.0mm
D21, D24, D41, D42: 1N4148; D_DO-35_SOD27_P7.62mm_Horizontal
D25, D46: 1N4007; D_DO-41_SOD81_P10.16mm_Horizontal
D26: LED_red; LED_D3.0mm
D27: 1N4007; D_DO-41_SOD81_P7.62mm_Horizontal
D28, D29, D38: 1N4148; D_DO-35_SOD27_P2.54mm_Vertical_AnodeUp
D30, D31, D32, D33, D34, D35, D36, D37: BAT85; D_DO-35_SOD27_P7.62mm_Horizontal
D40: BZX79C15; D_DO-35_SOD27_P7.62mm_Horizontal
D43: BZX79C10; D_DO-35_SOD27_P7.62mm_Horizontal
D45: 1N4744A; D_DO-41_SOD81_P10.16mm_Horizontal
F1: 5A; Fuseholder_Blade_Mini_Keystone_3568
F2: 1A; Fuseholder_Blade_Mini_Keystone_3568
H1, H2, H3, H4, H15, H16, H17, H18, H19: M3; MountingHole_3.2mm_M3
H5, H6, H7, H8, H9, H10, H11, H12, H13, H14: M2.5; MountingHole_2.7mm_M2.5
J1: TO PI (40-pin ribbon); IDC-Header_2x20_P2.54mm_Vertical
J2: POWER IN; PhoenixContact_MSTBA_2,5_3-G-5,08_1x03_P5.08mm_Horizontal
J3: TO 5V BUCK; PhoenixContact_MSTBA_2,5_2-G-5,08_1x02_P5.08mm_Horizontal
J4: SWITCHES; PhoenixContact_MSTBA_2,5_4-G-5,08_1x04_P5.08mm_Horizontal
J5: TACH; PhoenixContact_MSTBA_2,5_3-G-5,08_1x03_P5.08mm_Horizontal
J6: FUEL; PhoenixContact_MSTBA_2,5_2-G-5,08_1x02_P5.08mm_Horizontal
J7: HORN; PhoenixContact_MSTBA_2,5_2-G-5,08_1x02_P5.08mm_Horizontal
J8: SILENCE; PhoenixContact_MSTBA_2,5_2-G-5,08_1x02_P5.08mm_Horizontal
J9: MAX98357A MONO; PinSocket_1x07_P2.54mm_Vertical
J10: ADS1115 PWR/I2C; PinSocket_1x06_P2.54mm_Vertical
J11: LIGHTS; PhoenixContact_MSTBA_2,5_3-G-5,08_1x03_P5.08mm_Horizontal
J12: COIL; PhoenixContact_MSTBA_2,5_2-G-5,08_1x02_P5.08mm_Horizontal
J13: TILT; Molex_Micro-Fit_3.0_43650-0415_1x04_P3.00mm_Vertical
J14: TEMP PROBE; Molex_Micro-Fit_3.0_43650-0315_1x03_P3.00mm_Vertical
J15: ADS1115 INPUTS; PinSocket_1x06_P2.54mm_Vertical
J16: MAX98357A STEREO; PinSocket_1x06_P2.54mm_Vertical
J17: POD; Molex_Micro-Fit_3.0_43650-0815_1x08_P3.00mm_Vertical
J18: AUX (CHT + BRAKE); Molex_Micro-Fit_3.0_43045-0612_2x03_P3.00mm_Vertical
JP1: A=1-2 B=2-3; PinHeader_1x03_P2.54mm_Vertical
JP2: PULL-UP (A only); PinHeader_1x02_P2.54mm_Vertical
Q1, Q5: IRLZ44N; TO-220-3_Vertical
Q2: IRF4905; TO-220-3_Vertical
Q3, Q4: BC547B; TO-92_Inline_Wide
R1, R2, R22, R95: 3.3k; R_Axial_DIN0207_L6.3mm_D2.5mm_P7.62mm_Horizontal
R3, R35, R40, R67, R68, R89, R90, R91, R92, R96: 1k; R_Axial_DIN0207_L6.3mm_D2.5mm_P7.62mm_Horizontal
R4, R12, R13, R71, R74, R82: 470; R_Axial_DIN0207_L6.3mm_D2.5mm_P7.62mm_Horizontal
R11, R14, R16, R17, R18, R19, R97: 2.2k; R_Axial_DIN0207_L6.3mm_D2.5mm_P7.62mm_Horizontal
R15, R21, R31, R34, R51, R53, R63, R72, R94: 10k; R_Axial_DIN0207_L6.3mm_D2.5mm_P7.62mm_Horizontal
R20, R83, R84, R87, R93: 100; R_Axial_DIN0207_L6.3mm_D2.5mm_P7.62mm_Horizontal
R30, R33, R60, R62: 47k; R_Axial_DIN0207_L6.3mm_D2.5mm_P7.62mm_Horizontal
R32: 220; R_Axial_DIN0207_L6.3mm_D2.5mm_P7.62mm_Horizontal
R50, R52, R61, R86: 4.7k; R_Axial_DIN0207_L6.3mm_D2.5mm_P7.62mm_Horizontal
R64, R65, R70, R73: 100k; R_Axial_DIN0207_L6.3mm_D2.5mm_P7.62mm_Horizontal
R66: 1M; R_Axial_DIN0207_L6.3mm_D2.5mm_P7.62mm_Horizontal
R69: 220k; R_Axial_DIN0207_L6.3mm_D2.5mm_P7.62mm_Horizontal
R80, R81: 2.2k 1/2W; R_Axial_DIN0309_L9.0mm_D3.2mm_P12.70mm_Horizontal
R85, R88: 47; R_Axial_DIN0207_L6.3mm_D2.5mm_P7.62mm_Horizontal
TP1: +12V_IN; TestPoint_THTPad_D2.0mm_Drill1.0mm
TP2: +12V; TestPoint_THTPad_D2.0mm_Drill1.0mm
TP3: +12V_HORN; TestPoint_THTPad_D2.0mm_Drill1.0mm
TP4: +5V; TestPoint_THTPad_D2.0mm_Drill1.0mm
TP5: +3V3; TestPoint_THTPad_D2.0mm_Drill1.0mm
TP6, TP7, TP8: GND; TestPoint_Keystone_5005-5009_Compact
TP9: BATT_ADC; TestPoint_THTPad_D2.0mm_Drill1.0mm
TP10: FUEL_ADC; TestPoint_THTPad_D2.0mm_Drill1.0mm
TP11: OIL_GPIO; TestPoint_THTPad_D2.0mm_Drill1.0mm
TP12: FILT_SW; TestPoint_THTPad_D2.0mm_Drill1.0mm
TP13: TEMP_SW; TestPoint_THTPad_D2.0mm_Drill1.0mm
TP14: TACH_GPIO; TestPoint_THTPad_D2.0mm_Drill1.0mm
TP15: HORN_G; TestPoint_THTPad_D2.0mm_Drill1.0mm
TP16: BTN_GPIO; TestPoint_THTPad_D2.0mm_Drill1.0mm
TP17: +12V_BAT; TestPoint_THTPad_D2.0mm_Drill1.0mm
TP18: IGN; TestPoint_THTPad_D2.0mm_Drill1.0mm
TP19: HOLD_GPIO; TestPoint_THTPad_D2.0mm_Drill1.0mm
TP20: KILL_RC; TestPoint_THTPad_D2.0mm_Drill1.0mm
U1, U4, U5, U7, U8, U9, U10: PC817; DIP-4_W7.62mm
U6: CD4060BE; DIP-16_W7.62mm
U11: DS18B20; TO-92_Inline_Wide

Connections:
+3V3: D30.1 (K), D32.1 (K), D34.1 (K), D36.1 (K), J1.1, J1.17, J10.1, R4.1, R15.1, R32.1, R50.1, R52.1, R85.1, R86.2, R88.1, TP5.1, U11.3 (V_{DD})
+5V: J1.2, J1.4, J9.7, J16.1, R3.1, TP4.1
+12V: D46.1 (K), F2.1, J3.1, J5.1, J17.7, Q2.2 (D), R1.1, R11.1, R14.1, R30.1, R71.1, R95.1, R97.1, TP2.1
+12V_BAT: D1.1 (K), D40.1 (K), F1.2, Q2.3 (S), R60.1, TP17.1
+12V_HORN: D25.1 (K), F2.2, J7.1, R2.1, R22.1, TP3.1
+12V_IN: F1.1, J2.1, TP1.1
/COIL_CLAMP: C11.1, D45.1 (K), R81.2, R82.1
/COIL_IN: J12.1, R80.1
/COIL_MID: R80.2, R81.1
/FUEL_DIV: JP1.3 (B), R33.2, R34.1
/FUEL_IN: J6.1, JP1.1 (A), R33.1
/FUEL_SEL: JP1.2 (C), JP2.2 (B), R35.1
/HORN_DRAIN: D25.2 (A), D26.1 (K), J7.2, Q1.2 (D)
/LT_FRONT: J11.1, R17.1
/LT_REAR: J11.2, R18.1
/LT_WORK: J11.3, R19.1
/OIL_SW: D21.2 (A), J4.1, U1.2
/PWR_ON: Q3.2 (B), Q4.1 (C), R62.2, R63.2, R64.1
/TACH_SIG: D24.2 (A), J5.2, U4.2
/TMR_CT: C8.1, U6.9 (~Φ0)
/TMR_Q14: R68.1, U6.3 (Q14)
/TMR_RT: R70.1, U6.10 (Φ0)
/TMR_VDD: C9.1, D43.1 (K), R71.2, U6.16 (VDD)
BATT_ADC: C1.1, D30.2 (A), D31.1 (K), J15.5, R30.2, R31.1, TP9.1
BRAKE_GPIO: J1.21, R96.1
BTN_BACK_GPIO: C15.1, J1.19, R92.2
BTN_BACK_IN: J17.4, R92.1
BTN_GPIO: C3.1, J1.29, R40.2, TP16.1
BTN_IN: J8.1, J17.5, R40.1
BTN_L_GPIO: C12.1, J1.24, R89.2
BTN_L_IN: J17.1, R89.1
BTN_OK_GPIO: C14.1, J1.38, R91.2
BTN_OK_IN: J17.3, R91.1
BTN_R_GPIO: C13.1, J1.26, R90.2
BTN_R_IN: J17.2, R90.1
FAN_DRAIN: D46.2 (A), D47.1 (K), J17.8, Q5.2 (D)
FAN_GPIO: J1.23, R93.1
FILT_ADC: C4.1, D34.2 (A), D35.1 (K), J15.3, R51.2
FILT_LED: J1.16, R12.1
FILT_SW: J4.2, R50.2, R51.1, TP12.1
FUEL_ADC: C2.1, D32.2 (A), D33.1 (K), J15.4, R35.2, TP10.1
GND: C1.2, C2.2, C3.2, C4.2, C5.2, C7.2, C9.2, C10.2, C11.2, C12.2, C13.2, C14.2, C15.2, D1.2 (A), D2.1 (K), D3.1 (K), D4.1 (K), D5.1 (K), D12.1 (K), D13.1 (K), D17.1 (K), D27.2 (A), D28.2 (A), D29.2 (A), D31.2 (A), D33.2 (A), D35.2 (A), D37.2 (A), D38.2 (A), D43.2 (A), D45.2 (A), J1.6, J1.9, J1.14, J1.20, J1.25, J1.30, J1.34, J1.39, J2.3, J3.2, J4.4, J5.3, J6.2, J8.2, J9.6, J10.2, J10.5, J12.2, J13.1, J14.1, J16.2, J17.6, J18.1, Q1.3 (S), Q3.3 (E), Q4.3 (E), Q5.3 (S), R21.2, R31.2, R34.2, R64.2, R66.2, R73.2, R94.2, TP6.1, TP7.1, TP8.1, U1.3, U4.3, U5.2, U5.3, U6.8 (VSS), U7.2, U7.3, U8.2, U8.3, U9.2, U9.3, U10.2, U10.3, U11.1 (GND)
HOLD_GPIO: J1.37, R63.1, R74.1, TP19.1
HORN_G: Q1.1 (G), R20.2, R21.1, TP15.1
HORN_GPIO: J1.13, R20.1
I2S_BCLK: J1.12, J9.2, J16.3
I2S_DIN: J1.40, J9.3, J16.5
I2S_LRC: J1.35, J9.1, J16.4
IGN: D27.1 (K), J2.2, R16.1, R62.1, R72.1, TP18.1
KEY_GPIO: J1.31, U5.4
KILL_GPIO: J1.36, R67.1
KILL_RC: C7.1, D41.1 (K), D42.1 (K), R65.1, R66.1, TP20.1
LT_FRONT_GPIO: J1.22, U7.4
LT_REAR_GPIO: J1.32, U8.4
LT_WORK_GPIO: J1.33, U9.4
unnamed: C8.2, R69.2, R70.2
unnamed: D2.2 (A), R1.2
unnamed: D3.2 (A), R2.2
unnamed: D4.2 (A), R3.2
unnamed: D5.2 (A), R4.2
unnamed: D11.2 (A), D21.1 (K), R11.2
unnamed: D11.1 (K), U1.1
unnamed: D12.2 (A), R12.2
unnamed: D13.2 (A), R13.2
unnamed: D14.2 (A), D24.1 (K), R14.2
unnamed: D14.1 (K), U4.1
unnamed: D16.2 (A), R16.2
unnamed: D16.1 (K), U5.1
unnamed: D17.2 (A), R74.2
unnamed: D18.2 (A), D28.1 (K), R17.2
unnamed: D18.1 (K), U7.1
unnamed: D19.2 (A), D29.1 (K), R18.2
unnamed: D19.1 (K), U8.1
unnamed: D20.2 (A), D38.1 (K), R19.2
unnamed: D20.1 (K), U9.1
unnamed: D26.2 (A), R22.2
unnamed: D39.2 (A), R82.2
unnamed: D39.1 (K), U10.1
unnamed: D40.2 (A), Q2.1 (G), R60.2, R61.1
unnamed: D41.2 (A), R67.2
unnamed: D42.2 (A), R68.2
unnamed: D47.2 (A), R95.2
unnamed: J14.2, R87.2
unnamed: J14.3, R88.2
unnamed: J18.5, R96.2
unnamed: J18.6, R97.2
unnamed: JP2.1 (A), R32.2
unnamed: Q3.1 (C), R61.2
unnamed: Q4.2 (B), R65.2
unnamed: Q5.1 (G), R93.2, R94.1
unnamed: C10.1, R72.2, R73.1, U6.12 (CLR)
unnamed: R69.1, U6.11 (~Φ1)
OIL_GPIO: J1.15, TP11.1, U1.4
SCL: J1.5, J10.3, R84.1
SDA: J1.3, J10.4, R83.1
TACH_GPIO: J1.11, R15.2, TP14.1, U4.4, U10.4
TEMP_ADC: C5.1, D36.2 (A), D37.1 (K), J15.2, R53.2
TEMP_LED: J1.18, R13.1
TEMP_SW: J4.3, R52.2, R53.1, TP13.1
TILT_3V3: J13.2, J18.2, R85.2
TILT_SCL: J13.4, J18.4, R84.2
TILT_SDA: J13.3, J18.3, R83.2
W1_DQ: J1.7, R86.1, R87.1, U11.2 (DQ)

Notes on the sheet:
POWER IN / FUSES / PROTECTION / POWER LEDS
J2 BAT+ is the constant battery feed (7.5 A fuse at the battery). F1 5 A main, D1 TVS clamps spikes / blows F1 if reversed.
12V ON
HORN/F2
3V3
ENGINE + HYDRAULIC INPUTS (TACH, OIL, FILTER, TEMP)
Optocouplers: input active = yellow LED on = GPIO pulled low. Filter + temp: monitored on the ADC with a 4.7k resistor AT THE SWITCH (1.65 V OK, 0 V closed, 3.3 V wire broken).
HIGH VOLTAGE - IGNITION COIL
coil - spikes to ~400 V
connect the coil (J12) OR a Hall sensor (J5), not both
on = closed, blink = broken wire
POWER HOLD
Q2 passes +12V_BAT to +12V while Q3 is on: key on (IGN) OR Pi HOLD high. Q4 cuts it: Pi KILL at the end of shutdown, or the U6 timer ~3 min after key-off. C7 stretches a cut to a few seconds.
HOLD (Pi holding power)
U5 output low = key on
BATTERY / FUEL / BUTTON
ADC inputs clamp to 0..3.3 V. Fuel: A = sender only (JP1 1-2, JP2 on); B = gauge + dash (JP1 2-3, JP2 off).
battery / 5.7
LIGHTS ON (light sensing)
Sense wires from the LAMP side of each light switch (a few mA; the lamps' own current never comes here).
TEST POINTS
Same labels as the board silkscreen.
MOUNTING
M3: H1-4 corners, H15-18 sides, H19 centre. M2.5: H5-8 ADC, H9-10 mono, H11-14 stereo amp
BUTTON POD (rev 2.9)
J17 to the pod on the box top: 4 menu buttons and ALARM SILENCE to GND, and the pod's 12 V exhaust fan. Buttons filtered like SILENCE (1k + 100 nF). The Pi switches the fan through Q5; R94 keeps it off at boot.
J17: 1 LEFT 2 RIGHT 3 OK 4 BACK 5 SILENCE 6 GND 7 FAN +12V 8 FAN -
TILT SENSOR CONNECTOR (rev 2.6)
Latching Molex Micro-Fit 3.0. LSM6DSOX board on a short cable (under ~30-50 cm), on the same I2C bus as the ADS1115.
1 GND 2 3V3 3 SDA 4 SCL (cable soldered to the sensor board)
TEMPERATURE (rev 2.7)
1-Wire on GPIO 4. U11 (E-BOX TEMP SENSOR) measures the electronics box's air; J14 takes external DS18B20 probes (cab, outside). Several probes can share J14.
J14: 1 GND 2 DQ 3 3V3
TO RASPBERRY PI (40-pin ribbon, pin 1 to pin 1)
PLUG-IN MODULES
J10 + J15: ADS1115 (Adafruit 1085, two rows 12.7 mm apart)
J10 VIN GND SCL SDA ADDR ALRT; J15 A+ A3 A2 A1 A0 A-
A+ / A- are the module's own analog supply (outputs): left open
J9: MONO amp, Adafruit 3006 (LRC BCLK DIN GAIN SD GND VIN); J16: STEREO amp, Adafruit 6513
(VDD GND BCLK LRC DIN GAIN). Same signals: fit one amp only

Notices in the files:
README.md:
License:
MIT (see [`LICENSE`](LICENSE)): use it, change it and share it, board design included; keep the copyright
notice. **No warranty.** This is a hobby project for a 1978 machine, and the breakout board has not yet been
built and tested on real hardware. Check everything yourself before you wire it to a machine you care about.
